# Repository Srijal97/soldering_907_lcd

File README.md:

# Soldering Iron Controller for Hakko 907
This is a project based on 'Soldering Iron Controller for Hakko 907 v.2', by Alexander (sfrwmaker).
- [Hackster](https://www.hackster.io/sfrwmaker/soldering-iron-controller-for-hakko-907-v-2-fc75d7)
- [Instructables](http://www.instructables.com/id/Soldering-Iron-Controller-for-Hakko-907/)
- [GitHub](https://github.com/sfrwmaker/soldering_907_lcd)

A PCB with support for OLED display instead of 8x2 alphanumeric LCD has been made on eagle. The iron works great and heats to:
- 200C in 20secs
- 250C in 51secs
- 300C in 1min, 14secs
- 350C in 1min, 34secs

on a 19V DC Power Supply. It would be much faster on a 24V supply.

I have 5 extra PCBs left, which I won't be using. So, if anybody wants one, I'll send it to you for just the shipping cost from Mumbai, India to your place.

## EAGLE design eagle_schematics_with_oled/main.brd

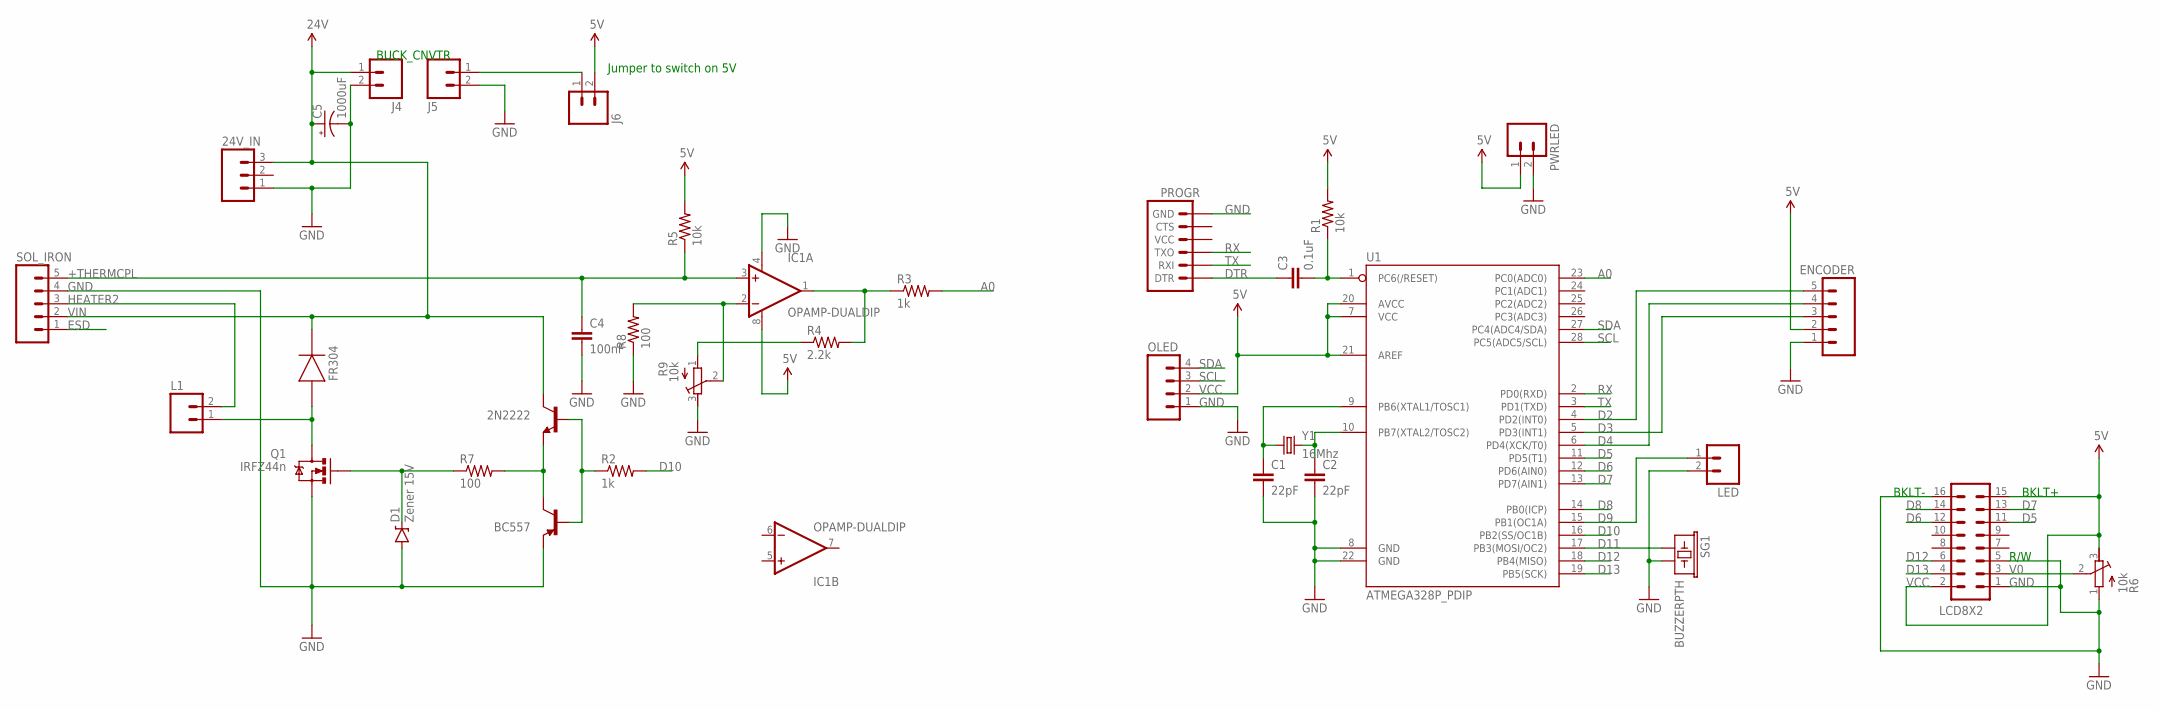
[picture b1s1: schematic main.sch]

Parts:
2N2222: TRANSISTOR_NPNP2N2222A; TO-92
24V_IN: M03PTH; 1X03
BC557: TRANSISTOR_PNPTO92; TO-92
C1, C2: 22pF; CAP-PTH-SMALL
C3: 0.1uF; CAP-PTH-SMALL
C4: 100nF; CAP-PTH-SMALL
C5: 1000uF; CPOL-RADIAL-1000UF-25V
D1: Zener 15V; DIODE-ZENER
ENCODER: M05PTH; 1X05
IC1: OPAMP-DUALDIP; DIP08
J4, J5, J6: M02PTH; 1X02
L1: M02PTH; 1X02
LCD8X2: M08X2; 2X8
LED: M02PTH; 1X02
OLED: M04PTH; 1X04
PROGR: ARDUINO_SERIAL_PROGRAMPTH; 1X06
PWRLED: M02PTH; 1X02
Q1: IRFZ44n; TO220V
R1, R5: 10k; AXIAL-0.4
R2, R3: 1k; AXIAL-0.4
R4: 2.2k; AXIAL-0.4
R6, R9: 10k; RTRIM3296W
R7, R8: 100; AXIAL-0.4
SG1: BUZZERPTH; BUZZER-12MM
SOL_IRON: M05PTH; 1X05
U1: ATMEGA328P_PDIP; DIL28-3
U$1: FR304
Y1: 16Mhz; HC49US

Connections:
+THERMCPL: C4.1, IC1.3 (+IN), R5.P$1 (1), SOL_IRON.5
A0: R3.P$2 (2), U1.23 (PC0(ADC0))
D2: ENCODER.5, U1.4 (PD2(INT0))
D3: ENCODER.3, U1.5 (PD3(INT1))
D4: ENCODER.4, U1.6 (PD4(XCK/T0))
D5: LCD8X2.11, U1.11 (PD5(T1))
D6: LCD8X2.12, U1.12 (PD6(AIN0))
D7: LCD8X2.13, U1.13 (PD7(AIN1))
D8: LCD8X2.14, U1.14 (PB0(ICP))
D9: LED.1, U1.15 (PB1(OC1A))
D10: R2.P$2 (2), U1.16 (PB2(SS/OC1B))
D11: SG1.+ (1), U1.17 (PB3(MOSI/OC2))
D12: LCD8X2.6, U1.18 (PB4(MISO))
D13: LCD8X2.4, U1.19 (PB5(SCK))
DTR: C3.1, PROGR.1 (DTR)
ESD: SOL_IRON.1
GND: 24V_IN.1, BC557.1 (E), C1.2, C2.2, C4.2, C5.-, D1.P$2 (A), ENCODER.1, IC1.4 (V-), J4.2, J5.2, LCD8X2.1, LCD8X2.5, LCD8X2.16, LED.2, OLED.1, PROGR.6 (GND), PWRLED.2, Q1.3 (S), R6.1 (A), R8.P$1 (1), R9.3 (E), SG1.- (2), SOL_IRON.4, U1.8 (GND), U1.22 (GND)
HEATER2: L1.2, SOL_IRON.3
unnamed: C1.1, U1.9 (PB6(XTAL1/TOSC1)), Y1.1
unnamed: C2.1, U1.10 (PB7(XTAL2/TOSC2)), Y1.2
unnamed: C3.2, R1.P$1 (1), U1.1 (PC6(/RESET))
unnamed: 2N2222.3 (E), BC557.3 (C), R7.P$2 (2)
unnamed: D1.P$1 (C), Q1.1 (G), R7.P$1 (1)
unnamed: L1.1, Q1.2 (D), U$1.A (ANODE)
unnamed: IC1.2 (-IN), R8.P$2 (2), R9.2 (S)
unnamed: 2N2222.2 (B), BC557.2 (B), R2.P$1 (1)
unnamed: IC1.1 (OUT), R3.P$1 (1), R4.P$2 (2)
unnamed: R4.P$1 (1), R9.1 (A)
unnamed: J5.1, J6.1
RX: PROGR.3 (TXO), U1.2 (PD0(RXD))
SCL: OLED.3, U1.28 (PC5(ADC5/SCL))
SDA: OLED.4, U1.27 (PC4(ADC4/SDA))
TX: PROGR.2 (RXI), U1.3 (PD1(TXD))
V0: LCD8X2.3, R6.2 (S)
VCC: ENCODER.2, IC1.8 (V+), J6.2, LCD8X2.2, LCD8X2.15, OLED.2, PWRLED.1, R1.P$2 (2), R5.P$2 (2), R6.3 (E), U1.7 (VCC), U1.20 (AVCC), U1.21 (AREF)
VIN: 2N2222.1 (C), 24V_IN.3, C5.+, J4.1, SOL_IRON.2, U$1.K (CATHODE)

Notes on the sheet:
BKLT+
BKLT-
R/W
BUCK_CNVTR
Jumper to switch on 5V

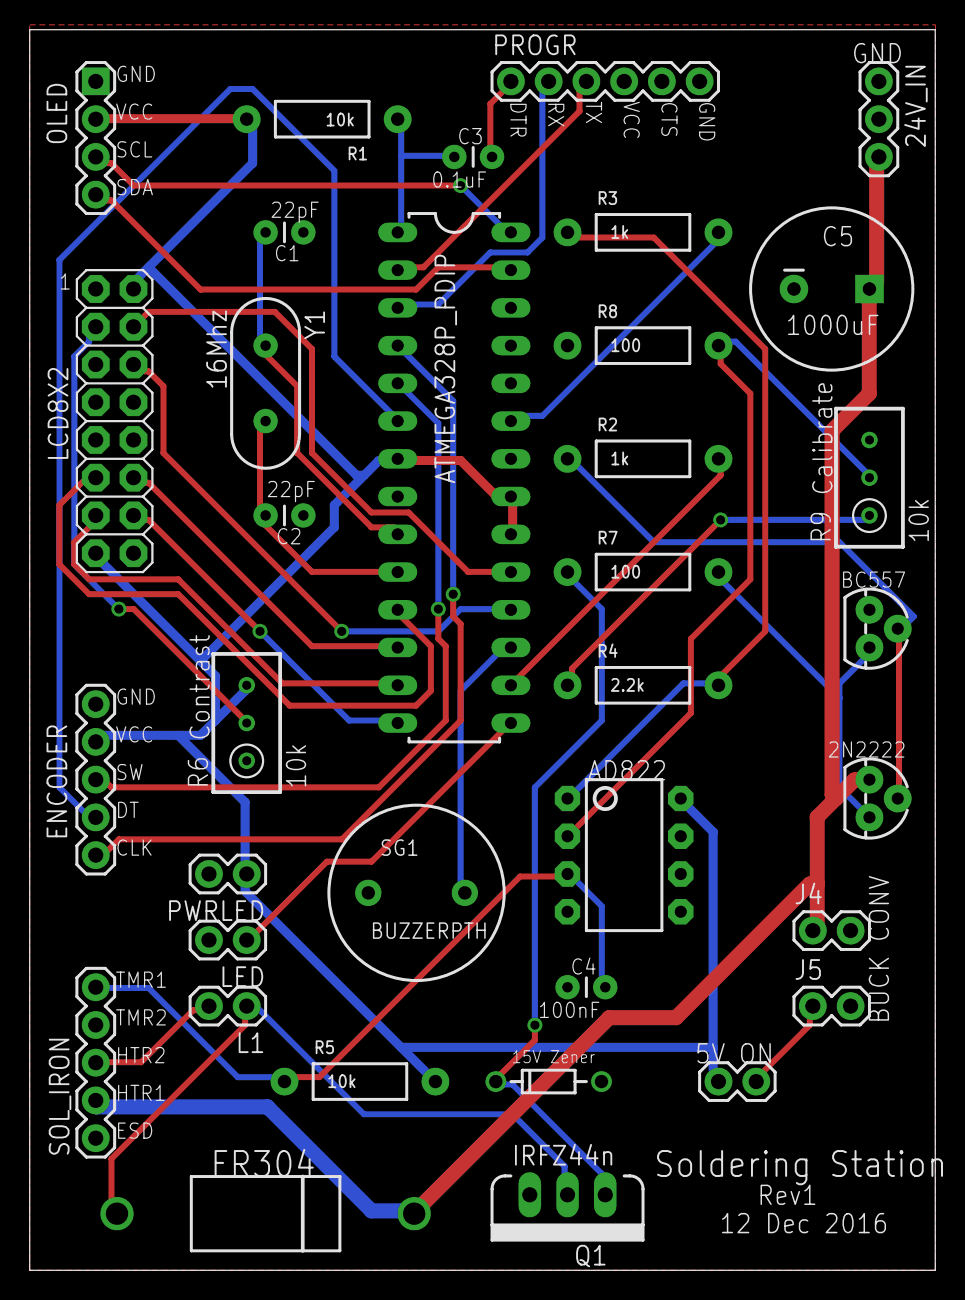
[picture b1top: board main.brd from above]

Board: 2 copper layers, 60.9 x 83.5 mm, 35 parts (0 on the bottom side), 35 nets.

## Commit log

2017-12-03 Added eagle schematics for board with OLED support
2017-12-09 Added images of build

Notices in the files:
parts and their libraries:
SparkFun-Connectors: Licensing: Creative Commons ShareAlike 4.0 International - https://creativecommons.org/licenses/by-sa/4.0
